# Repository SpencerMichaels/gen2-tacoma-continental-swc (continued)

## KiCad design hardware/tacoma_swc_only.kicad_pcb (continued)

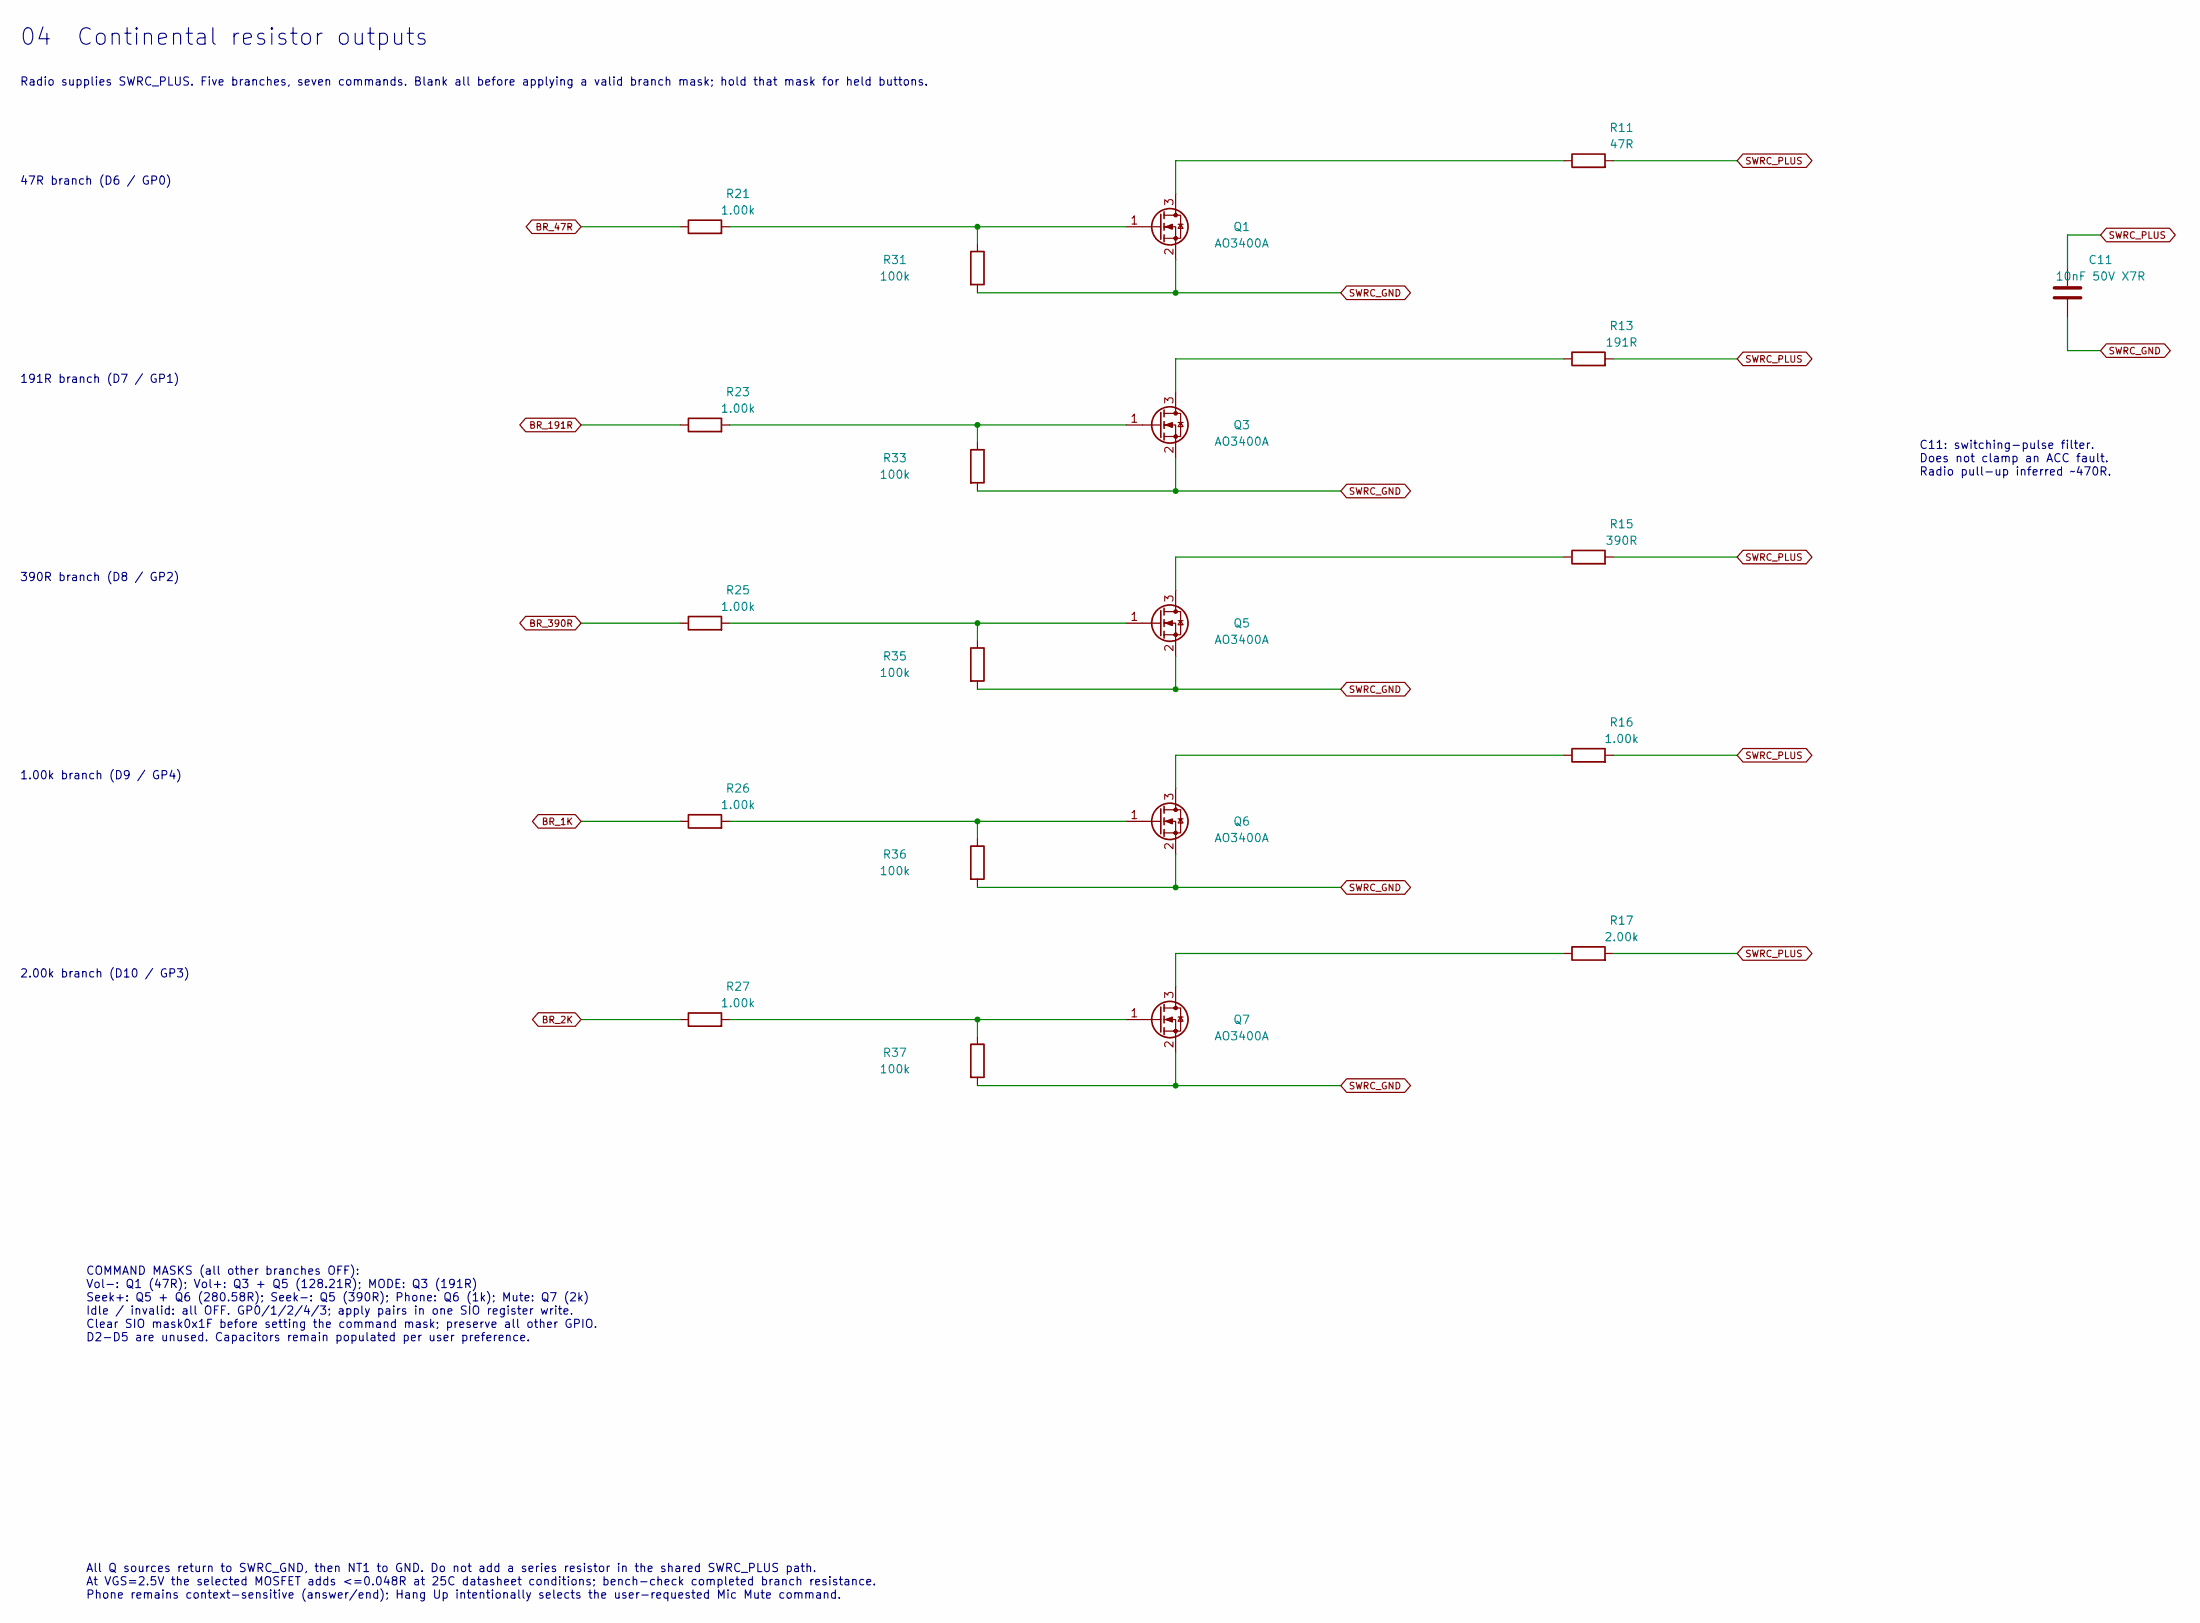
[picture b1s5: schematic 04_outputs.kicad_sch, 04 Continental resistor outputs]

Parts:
C11: 10nF 50V X7R; C_0805_2012Metric; MPN C0805C103K5RACTU
Q1, Q3, Q5, Q6, Q7: AO3400A; SOT-23; MPN AO3400A
R11: 47R; R_0805_2012Metric; MPN RC0805FR-0747RL
R13: 191R; R_0805_2012Metric; MPN RC0805FR-07191RL
R15: 390R; R_0805_2012Metric; MPN RC0805FR-07390RL
R16, R21, R23, R25, R26, R27: 1.00k; R_0805_2012Metric; MPN RC0805FR-071KL
R17: 2.00k; R_0805_2012Metric; MPN RC0805FR-072KL
R31, R33, R35, R36, R37: 100k; R_0805_2012Metric; MPN RC0805FR-07100KL

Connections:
BR_1K: R26.1; also elsewhere on the board
BR_2K: R27.1; also elsewhere on the board
BR_47R: R21.1; also elsewhere on the board
BR_191R: R23.1; also elsewhere on the board
BR_390R: R25.1; also elsewhere on the board
unnamed: Q1.3 (D), R11.1
unnamed: Q1.1 (G), R21.2, R31.1
unnamed: Q3.3 (D), R13.1
unnamed: Q3.1 (G), R23.2, R33.1
unnamed: Q5.3 (D), R15.1
unnamed: Q5.1 (G), R25.2, R35.1
unnamed: Q6.3 (D), R16.1
unnamed: Q6.1 (G), R26.2, R36.1
unnamed: Q7.3 (D), R17.1
unnamed: Q7.1 (G), R27.2, R37.1
SWRC_GND: C11.2, Q1.2 (S), Q3.2 (S), Q5.2 (S), Q6.2 (S), Q7.2 (S), R31.2, R33.2, R35.2, R36.2, R37.2; also elsewhere on the board
SWRC_PLUS: C11.1, R11.2, R13.2, R15.2, R16.2, R17.2; also elsewhere on the board

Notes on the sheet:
04 Continental resistor outputs
Radio supplies SWRC_PLUS. Five branches, seven commands. Blank all before applying a valid branch mask; hold that mask for held buttons.
C11: switching-pulse filter. Does not clamp an ACC fault. Radio pull-up inferred ~470R.
47R branch (D6 / GP0)
191R branch (D7 / GP1)
390R branch (D8 / GP2)
1.00k branch (D9 / GP4)
2.00k branch (D10 / GP3)
COMMAND MASKS (all other branches OFF): Vol-: Q1 (47R); Vol+: Q3 + Q5 (128.21R); MODE: Q3 (191R) Seek+: Q5 + Q6 (280.58R); Seek-: Q5 (390R); Phone: Q6 (1k); Mute: Q7 (2k) Idle / invalid: all OFF. GP0/1/2/4/3; apply pairs in one SIO register write. Clear SIO mask0x1F before setting the command mask;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
All Q sources return to SWRC_GND, then NT1 to GND. Do not add a series resistor in the shared SWRC_PLUS path. At VGS=2.5V the selected MOSFET adds <=0.048R at 25C datasheet conditions; bench-check completed branch resistance. Phone remains context-sensitive (answer/end); Hang Up intentionally selec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

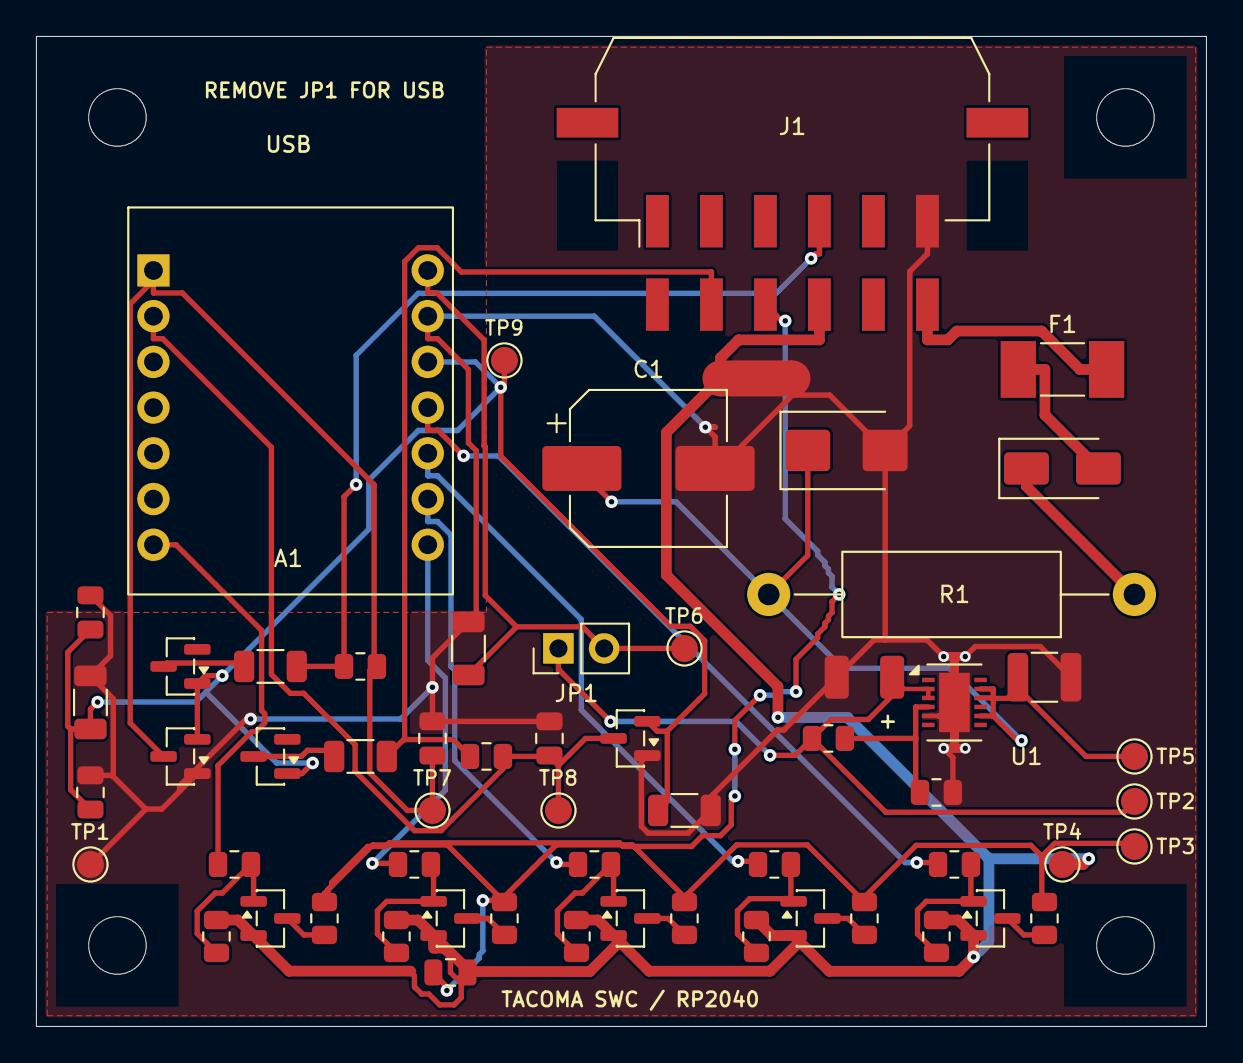
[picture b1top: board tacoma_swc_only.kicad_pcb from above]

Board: 2 copper layers, 65.0 x 55.0 mm, 63 parts (0 on the bottom side), 32 nets.

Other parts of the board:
H1, H2, H3, H4: M3; MountingHole_3.2mm_M3

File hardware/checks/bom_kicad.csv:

"Refs","Value","Footprint","Qty","DNP"
"A1","XIAO RP2040 (standard)","Tacoma_Mechanical:XIAO_RP2040_Socket_2x7","1",""
"C1","47uF / 63V","Capacitor_SMD:CP_Elec_8x10.5","1",""
"C2","10uF 63V X7R","Capacitor_SMD:C_1210_3225Metric","1",""
"C3","22uF 25V polymer","Capacitor_Tantalum_SMD:CP_EIA-3528-21_Kemet-B","1",""
"C4","10uF 25V X7R","Capacitor_SMD:C_1206_3216Metric","1",""
"C5","10nF 50V X7R","Capacitor_SMD:C_0805_2012Metric","1",""
"C6","10nF 50V X7R","Capacitor_SMD:C_0805_2012Metric","1",""
"C7","10uF 25V X7R","Capacitor_SMD:C_1206_3216Metric","1",""
"C8","100nF 50V X7R","Capacitor_SMD:C_0805_2012Metric","1",""
"C10","2.2uF 16V X7R","Capacitor_SMD:C_0805_2012Metric","1",""
"C11","10nF 50V X7R","Capacitor_SMD:C_0805_2012Metric","1",""
"D1","STPS1H100A","Diode_SMD:D_SMA","1",""
"D2","SMBJ24A","Diode_SMD:D_SMB","1",""
"D5","BAS70","Package_TO_SOT_SMD:SOT-23","1",""
"D6","BAS70","Package_TO_SOT_SMD:SOT-23","1",""
"D7","BAS70-04","Package_TO_SOT_SMD:SOT-23","1",""
"D8","BAS70-04","Package_TO_SOT_SMD:SOT-23","1",""
"F1","250mA fast / 125V","Tacoma_Mechanical:Littelfuse_451_6.1x2.69mm","1",""
"J1","Molex 43045-1209","Tacoma_Mechanical:Molex_43045_12_SMT_SeparateRetentionPads","1",""
"JP1","RUN power / REMOVE FOR USB","Connector_PinHeader_2.54mm:PinHeader_1x02_P2.54mm_Vertical","1",""
"NT1","SWRC return bond","NetTie:NetTie-2_SMD_Pad2.0mm","1",""
"Q1","AO3400A","Package_TO_SOT_SMD:SOT-23","1",""
"Q3","AO3400A","Package_TO_SOT_SMD:SOT-23","1",""
"Q5","AO3400A","Package_TO_SOT_SMD:SOT-23","1",""
"Q6","AO3400A","Package_TO_SOT_SMD:SOT-23","1",""
"Q7","AO3400A","Package_TO_SOT_SMD:SOT-23","1",""
"R1","10R / 1W","Resistor_THT:R_Axial_DIN0414_L11.9mm_D4.5mm_P20.32mm_Horizontal","1",""
"R2","30.1k 0.1%","Resistor_SMD:R_0805_2012Metric","1",""
"R3","10.0k 0.1%","Resistor_SMD:R_0805_2012Metric","1",""
"R4","330R","Resistor_SMD:R_1206_3216Metric","1",""
"R5","2.20k","Resistor_SMD:R_1206_3216Metric","1",""
"R6","2.20k","Resistor_SMD:R_1206_3216Metric","1",""
"R7","22.0k","Resistor_SMD:R_0805_2012Metric","1",""
"R8","22.0k","Resistor_SMD:R_0805_2012Metric","1",""
"R11","47R","Resistor_SMD:R_0805_2012Metric","1",""
"R13","191R","Resistor_SMD:R_0805_2012Metric","1",""
"R15","390R","Resistor_SMD:R_0805_2012Metric","1",""
"R16","1.00k","Resistor_SMD:R_0805_2012Metric","1",""
"R17","2.00k","Resistor_SMD:R_0805_2012Metric","1",""
"R21","1.00k","Resistor_SMD:R_0805_2012Metric","1",""
"R23","1.00k","Resistor_SMD:R_0805_2012Metric","1",""
"R25","1.00k","Resistor_SMD:R_0805_2012Metric","1",""
"R26","1.00k","Resistor_SMD:R_0805_2012Metric","1",""
"R27","1.00k","Resistor_SMD:R_0805_2012Metric","1",""
"R31","100k","Resistor_SMD:R_0805_2012Metric","1",""
"R33","100k","Resistor_SMD:R_0805_2012Metric","1",""
"R35","100k","Resistor_SMD:R_0805_2012Metric","1",""
"R36","100k","Resistor_SMD:R_0805_2012Metric","1",""
"R37","100k","Resistor_SMD:R_0805_2012Metric","1",""
"TP1","GND","TestPoint:TestPoint_Pad_D1.5mm","1",""
"TP2","REG5","TestPoint:TestPoint_Pad_D1.5mm","1",""
"TP3","SWRC_PLUS","TestPoint:TestPoint_Pad_D1.5mm","1",""
"TP4","SWRC_GND","TestPoint:TestPoint_Pad_D1.5mm","1",""
"TP5","ACC_CLAMP","TestPoint:TestPoint_Pad_D1.5mm","1",""
"TP6","+5V_MODULE","TestPoint:TestPoint_Pad_D1.5mm","1",""
"TP7","ADC_SW1","TestPoint:TestPoint_Pad_D1.5mm","1",""
"TP8","ADC_SW2","TestPoint:TestPoint_Pad_D1.5mm","1",""
"TP9","+3V3_SENSE","TestPoint:TestPoint_Pad_D1.5mm","1",""
"U1","LT3012EDE","Package_DFN_QFN:DFN-12-1EP_3x4mm_P0.5mm_EP1.7x3.3mm","1",""

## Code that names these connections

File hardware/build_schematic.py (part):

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        (HERE/(self.name+'.kicad_sch')).write_text(dump(root)+'\n')

if __name__=='__main__' and '--pins' in __import__('sys').argv:
    for s in [NANO,REG5,MOS,BAS,CLAMP,BUF,TIE,D]:print(s,json.dumps(pins_for(s),indent=1))
    raise SystemExit

RES0805='Resistor_SMD:R_0805_2012Metric'
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cap(s,'C10',60.96,147.32,'2.2uF 16V X7R','+3V3_SENSE')
testpoint(s,'TP9',157.48,147.32,'+3V3_SENSE')
s.comp('NT1',TIE,73.66,177.8,{'1':'SWRC_GND','2':'GND'},'SWRC return bond',footprint='NetTie:NetTie-2_SMD_Pad2.0mm',note='Copper net tie; output returns route to J1 pin 10')
cap(s,'C7',205.74,177.8,'10uF 16V X7R','+3V3_SENSE')
cap(s,'C8',279.4,177.8,'100nF 16V X7R','+3V3_SENSE')
resistor(s,'R4',350.52,177.8,'330R','+3V3_SENSE','GND',fp=RES1206,note='1%,0.25W;3V3 rail bleed for input clamp current')
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s.comp('C1',CP,48.26,106.68,{'1':'ACC_CLAMP','2':'GND'},'47uF / 63V',footprint='',note='105C electrolytic; final case size pending')
cap(s,'C2',134.62,106.68,'10uF 63V X7R','ACC_CLAMP',fp='Capacitor_SMD:C_1210_3225Metric')
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s.comp('C3',CP,350.52,106.68,{'1':'REG5','2':'GND'},'22uF 25V polymer',footprint='',note='Polarized: pin1 positive; 105C, 100mOhm ESR; stable capacitance under DC bias')
resistor(s,'R2',48.26,157.48,'30.1k 0.1%','REG5','REG_FB',note='0.1%, 25ppm/C feedback upper')
resistor(s,'R3',147.32,157.48,'10.0k 0.1%','REG_FB','GND',note='0.1%, 25ppm/C feedback lower')
s.comp('JP1',JUMPER,251.46,157.48,{'1':'REG5','2':'+5V_MODULE'},'REMOVE FOR USB',note='Remove shunt before USB; fitted for vehicle operation')
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for row,(i,name,val,gpio) in enumerate(branches):
    y=45.72+row*30.48; drain='OUT_D'+str(i); gate='OUT_G'+str(i)
    s.text(15.24,y-7.62,f'{val} branch ({gpio})',1.27)
    cr=s.comp('R'+str(10+i),R,256.54,y-10.16,{'1':drain,'2':'SWRC_PLUS'},val,angle=90,footprint=RES0805,note='1%, command resistor; user empirically verified window',autolabel=False)
    q=s.comp('Q'+str(i),MOS,190.5,y,{'1':gate,'2':'SWRC_GND','3':drain},'AO3400A',mpn='AO3400A',note='G=1 S=2 D=3; output active HIGH',autolabel=False)
    gr=s.comp('R'+str(20+i),R,120.65,y,{'1':'BR_'+name,'2':gate},'1.00k',angle=90,footprint=RES0805,note='1%, gate series resistor',autolabel=False)
    pd=s.comp('R'+str(30+i),R,162.56,y+6.35,{'1':gate,'2':'SWRC_GND'},'100k',footprint=RES0805,note='1%, gate-source pulldown; reset default OFF',autolabel=False,fields=[(149.86,y+5.08),(149.86,y+7.62)])
    s.wire(gr['1'],(101.6,y)); s.label((101.6,y),'BR_'+name,180)
    s.wire(gr['2'],(162.56,y)); s.wire((162.56,y),q['1']); s.wire((162.56,y),pd['1']); s.junction((162.56,y))
    s.wire(q['3'],(193.04,y-10.16)); s.wire((193.04,y-10.16),cr['1'])
    s.wire(cr['2'],(279.4,y-10.16)); s.label((279.4,y-10.16),'SWRC_PLUS')
    s.wire(q['2'],(193.04,y+10.16)); s.wire(pd['2'],(193.04,y+10.16)); s.junction((193.04,y+10.16))
    s.wire((193.04,y+10.16),(218.44,y+10.16)); s.label((218.44,y+10.16),'SWRC_GND')
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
